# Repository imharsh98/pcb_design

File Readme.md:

# PCB Design Internship

## Overview

This repository contains the complete PCB schematics and layouts for digital circuits (555 flasher, arduino microcontroller, decade counter, voltage regulator), ensuring correct pin-mapping and power integrity. This work was undertaken during an internship which the author attended for his BTech requirements. The internship was done at the company named Core Future.

## Repository Structure

```

├── designs/
│   ├── 555flasher/
    │   ├── 555flasher.brd                          # Board file for the 555flasher project
    │   ├── 555flasher.sch                          # Schematic file for the 555flasher project
    |
    ├── arduino/
    │   ├── arduino.brd    
    │   ├── arduino.sch
    |
    ├── decade_counter/
    │   ├── d_counter.brd   
    │   ├── d_counter.sch
    |   ├── d_counter_brd.png                       # PNG file of the decade counter schematic
    | 
    ├── voltage_regulator/
    │   ├── v_regulator.brd
        ├── v_regulator.sch                
│
├── pcb designs/
│   └── contains library files
|
├── practice-designs/
│   └── contains some unorganized practice designs and can be ignored
│
├── README.md                                       # This file (main guide)
```

## Project 1: 555 Timer LED Flasher (`555flasher.brd`)

*   **Description:** An astable multivibrator circuit using the LM555 timer.
*   **Highlights:** Ground plane implementation and power trace width management.

## Project 2: Arduino Compatible Board (`arduino.brd`)

*   **Description:** A custom microcontroller board layout based on the Arduino architecture.
*   **Highlights:**
    *   **Clock Stability:** Optimized placement of the Crystal Oscillator near the MCU.
    *   **Power Integrity:** Strategic placement of decoupling capacitors.

## Project 3: Digital Counter (`d_counter.brd`)

*   **Description:** A digital logic circuit for counting applications.
*   **Highlights:**
    *   **Signal Routing:** Managed routing for multiple logic gates and clock lines.

## Project 4: Voltage Regulator (`v_regulator.brd`)

*   **Description:** A power supply circuit designed to provide a stable DC output from a varying input voltage.
*   **Highlights:**
    *   **Thermal Management:** Copper polygon pours utilized for heat dissipation.
    *   **Power Routing:** Wide traces designed for high-current paths to minimize voltage drop.

---
### General Technical Details
*   **Tool Used:** Eagle CAD for layout and PnR (Placement and Routing); Proteus for circuit schematic creation.
*   **Steps for Replication:** Run the .sch file in Proteus and the .brd file in Eagle CAD. 
*   **Board Specs:** 2-Layer PCBs (Top/Bottom Copper)
*   **DFM:** Designed with through-hole components for ease of prototyping.

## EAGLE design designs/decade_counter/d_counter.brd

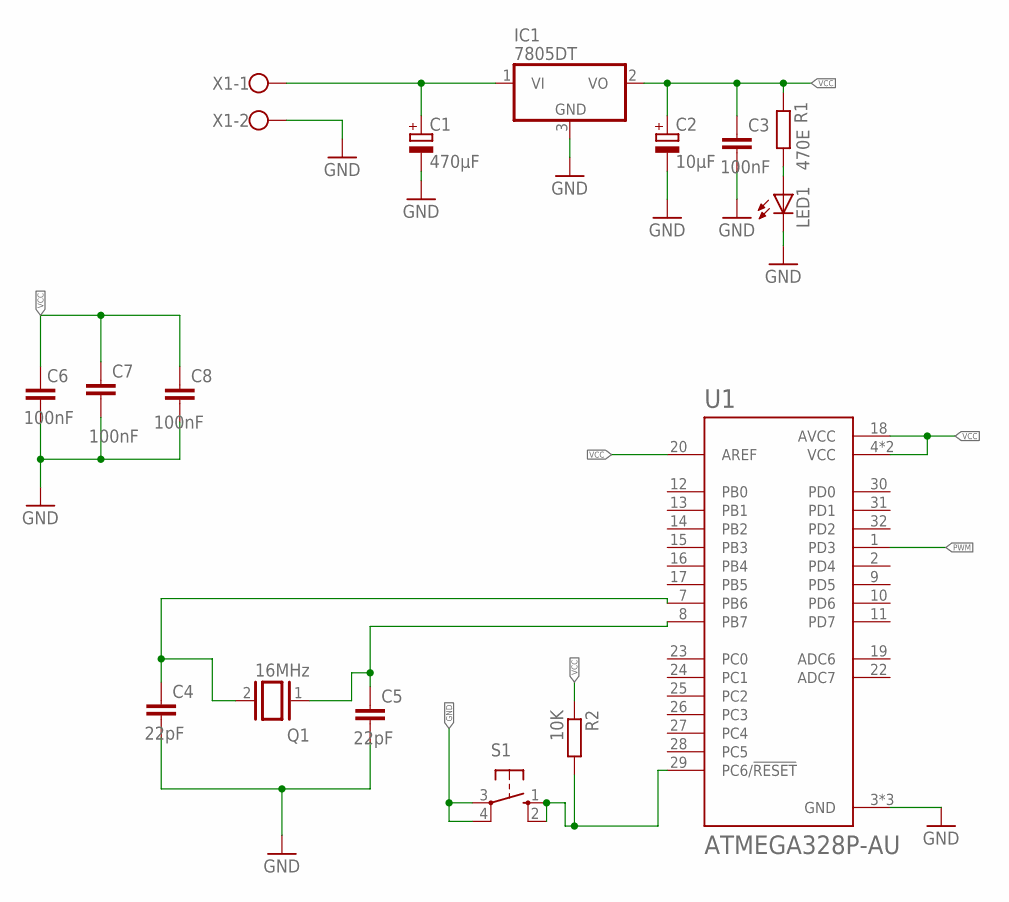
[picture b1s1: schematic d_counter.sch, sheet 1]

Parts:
C1: 470µF; 150CLZ-1010
C2: 10µF; 150CLZ-1010
C3, C6, C7, C8: 100nF; C1206
C4, C5: 22pF; C1206
IC1: 7805DT; TO252
LED1: LEDSMT1206; 1206
Q1: 16MHz; QS
R1: 470E; M1206
R2: 10K; R1206
S1: 10-XX; B3F-10XX
U1: ATMEGA328P-AU; QFP80P900X900X120-32N
X1: W237-102

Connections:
GND: C1.-, C2.-, C3.2, C4.2, C5.2, C6.2, C7.2, C8.2, IC1.3 (GND), LED1.C, S1.3, S1.4 (P1), U1.3 (GND), U1.5 (GND), U1.21 (GND), X1.2; also elsewhere on the board
unnamed: C1.+, IC1.1 (VI), X1.1
unnamed: LED1.A, R1.2
unnamed: C4.1, Q1.2, U1.7 (PB6)
unnamed: C5.1, Q1.1, U1.8 (PB7)
unnamed: R2.2, S1.1 (S), S1.2 (S1), U1.29 (PC6/!RESET)
PWM: U1.1 (PD3); also elsewhere on the board
VCC: C2.+, C3.1, C6.1, C7.1, C8.1, IC1.2 (VO), R1.1, R2.1, U1.4 (VCC), U1.6 (VCC), U1.18 (AVCC), U1.20 (AREF); also elsewhere on the board

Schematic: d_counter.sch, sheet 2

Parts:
IC2: 74AC08D; SO14
IC3, IC4, IC5, IC6: 4017D; SO16
LED2, LED3, LED4, LED5, LED6, LED7, LED8, LED9, LED10, LED11, LED12, LED13, LED14, LED15, LED16, LED17, LED18, LED19, LED20, LED21, LED22, LED23, LED24, LED25, LED26, LED27, LED28, LED29, LED30, LED31, LED32, LED33: LEDSML1206; SML1206
R3: 330E; R1206

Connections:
1: IC3.15 (RES), IC6.11 (Q9)
2: IC2.3 (O), IC4.14 (CLK)
3: IC3.3 (Q0), IC4.15 (RES)
4: IC2.6 (O), IC5.14 (CLK)
5: IC4.3 (Q0), IC5.15 (RES)
6: IC2.8 (O), IC6.14 (CLK)
7: IC5.3 (Q0), IC6.15 (RES)
8: IC3.2 (Q1), LED2.A
9: IC3.4 (Q2), LED3.A
10: IC3.7 (Q3), LED4.A
11: IC3.10 (Q4), LED5.A
12: IC3.1 (Q5), LED6.A
13: IC3.5 (Q6), LED7.A
14: IC3.6 (Q7), LED8.A
15: IC3.9 (Q8), LED9.A
16: IC4.2 (Q1), LED10.A
17: IC4.4 (Q2), LED11.A
18: IC4.7 (Q3), LED12.A
19: IC4.10 (Q4), LED13.A
20: IC4.1 (Q5), LED14.A
21: IC4.5 (Q6), LED15.A
22: IC4.6 (Q7), LED16.A
23: IC4.9 (Q8), LED17.A
24: IC5.2 (Q1), LED18.A
25: IC5.4 (Q2), LED19.A
26: IC5.7 (Q3), LED20.A
27: IC5.10 (Q4), LED21.A
28: IC5.1 (Q5), LED22.A
29: IC5.5 (Q6), LED23.A
30: IC5.6 (Q7), LED24.A
31: IC5.9 (Q8), LED25.A
32: IC6.2 (Q1), LED26.A
33: IC6.4 (Q2), LED27.A
34: IC6.7 (Q3), LED28.A
35: IC6.10 (Q4), LED29.A
36: IC6.1 (Q5), LED30.A
37: IC6.5 (Q6), LED31.A
38: IC6.6 (Q7), LED32.A
39: IC6.9 (Q8), LED33.A
GND: IC2.7 (GND), IC3.8 (VSS), IC4.8 (VSS), IC5.8 (VSS), IC6.8 (VSS), IC6.13 (ENA), R3.1; also elsewhere on the board
unnamed: IC2.1 (I0), IC3.11 (Q9), IC3.13 (ENA)
unnamed: IC2.4 (I0), IC4.11 (Q9), IC4.13 (ENA)
unnamed: IC2.9 (I0), IC5.11 (Q9), IC5.13 (ENA)
unnamed: LED2.C, LED3.C, LED4.C, LED5.C, LED6.C, LED7.C, LED8.C, LED9.C, LED10.C, LED11.C, LED12.C, LED13.C, LED14.C, LED15.C, LED16.C, LED17.C, LED18.C, LED19.C, LED20.C, LED21.C, LED22.C, LED23.C, LED24.C, LED25.C, LED26.C, LED27.C, LED28.C, LED29.C, LED30.C, LED31.C, LED32.C, LED33.C, R3.2
PWM: IC2.2 (I1), IC2.5 (I1), IC2.10 (I1), IC3.14 (CLK); also elsewhere on the board
VCC: IC2.14 (VCC), IC3.16 (VDD), IC4.16 (VDD), IC5.16 (VDD), IC6.16 (VDD); also elsewhere on the board

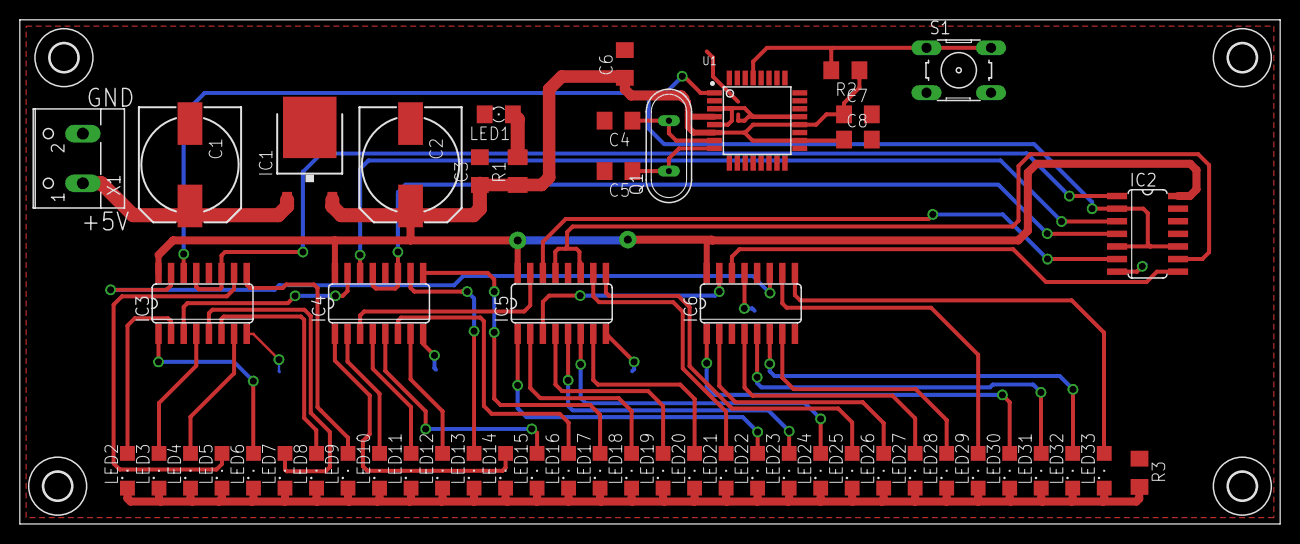
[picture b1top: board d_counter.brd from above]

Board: 2 copper layers, 127.0 x 50.8 mm, 58 parts (0 on the bottom side), 51 nets.

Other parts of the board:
U$1, U$2, U$3, U$5: 2,8

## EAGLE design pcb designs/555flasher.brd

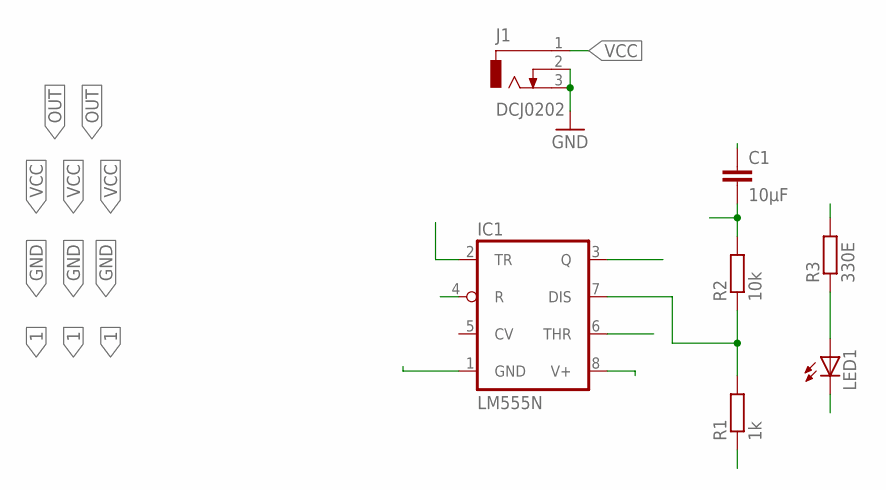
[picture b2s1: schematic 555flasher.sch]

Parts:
C1: 10µF; C025-025X050
IC1: LM555N; DIL08
J1: DCJ0202
LED1: LED5MM
R1: 1k; 0207/10
R2: 10k; 0207/10
R3: 330E; 0207/10

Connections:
1: C1.2, IC1.2 (TR), IC1.6 (THR), R2.2
GND: C1.1, IC1.1 (GND), J1.2, J1.3, LED1.K (C)
unnamed: IC1.7 (DIS), R1.2, R2.1
unnamed: LED1.A, R3.1
OUT: IC1.3 (Q), R3.2
VCC: IC1.4 (R), IC1.8 (V+), J1.1, R1.1

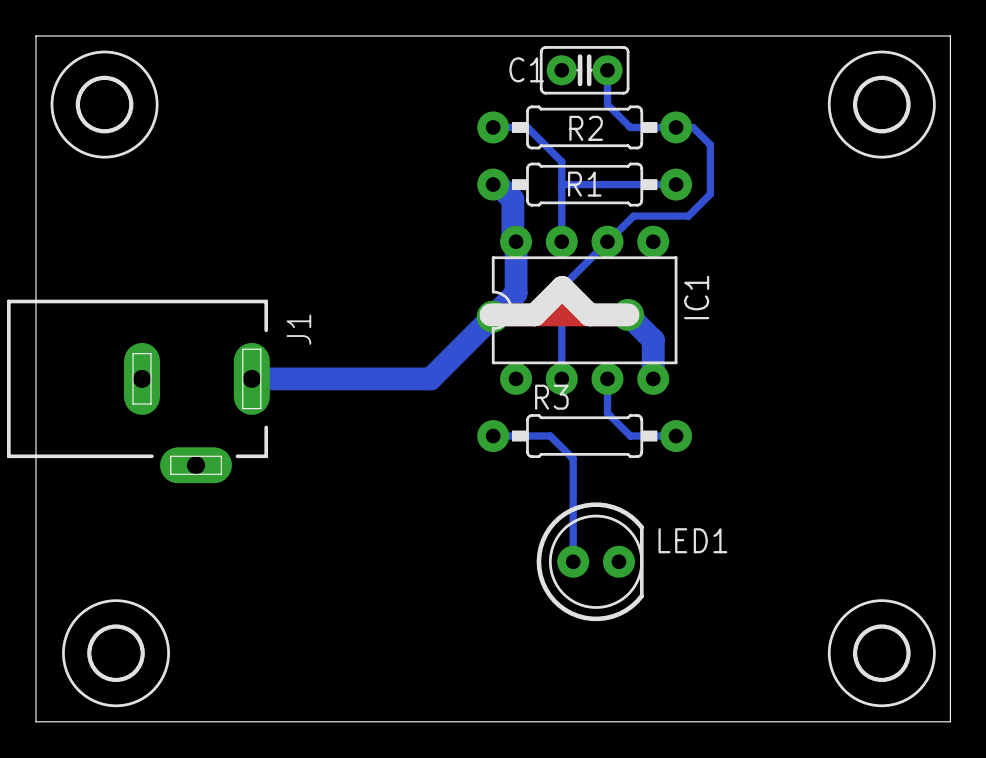
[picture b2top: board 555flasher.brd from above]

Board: 2 copper layers, 50.8 x 38.1 mm, 11 parts (0 on the bottom side), 6 nets.

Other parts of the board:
U$1, U$2, U$3, U$4: 2,8

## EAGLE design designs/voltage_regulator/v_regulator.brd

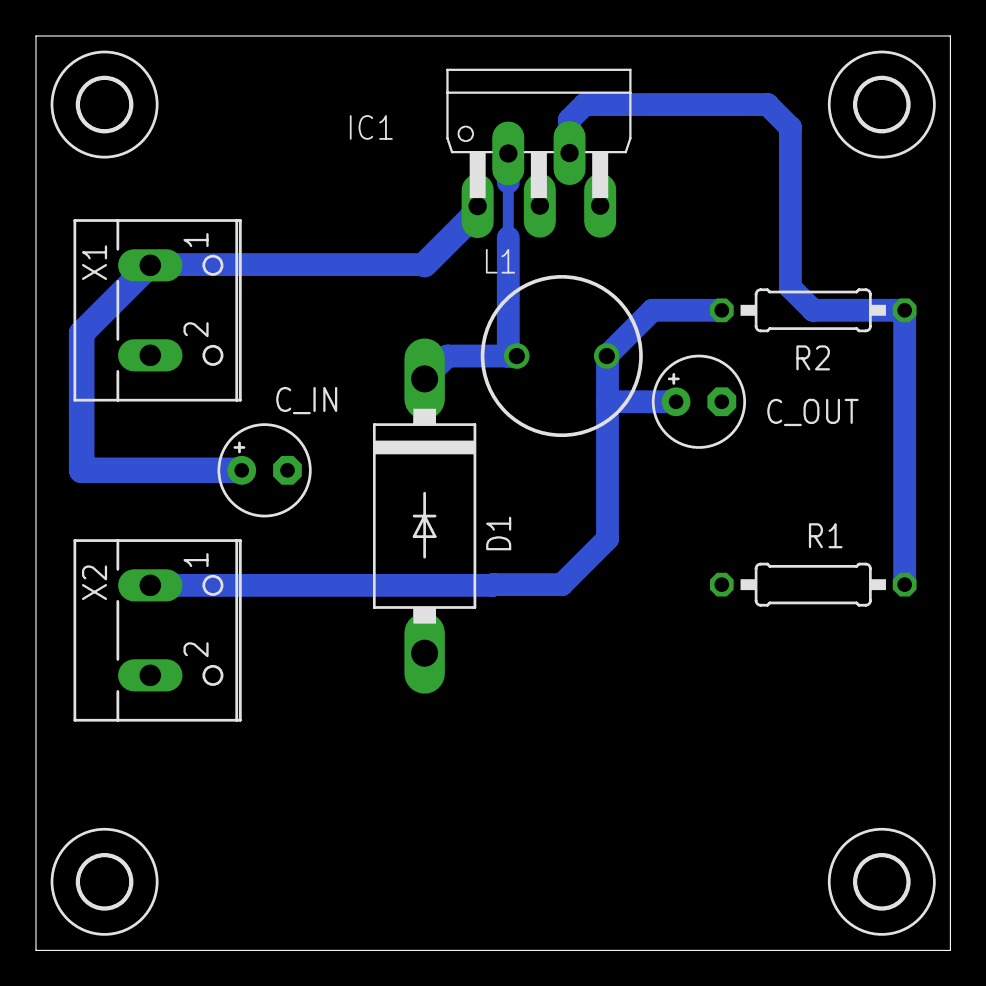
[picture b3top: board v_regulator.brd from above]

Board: 2 copper layers, 50.8 x 50.8 mm, 13 parts (0 on the bottom side), 5 nets.

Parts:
C_IN: 100µF; E2,5-5
C_OUT: 469µF; E2,5-5
D1: 1N5624; DO201-15
IC1: TO220-5_STAGGERED
L1: 68µH; 6000-XXXX-RC
R1: 3.6k; 0207/10
R2: 11k; 0207/10
U$1, U$2, U$3, U$4: 2,8
X1: 12V; W237-102
X2: W237-102

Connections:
GND: C_IN.-, C_OUT.-, D1.A, IC1.P$3, IC1.P$5, R1.1, X1.2, X2.2
unnamed: D1.C, IC1.P$2, L1.1
unnamed: IC1.P$4, R1.2, R2.1
V_IN: C_IN.+, IC1.P$1, X1.1
V_OUT: C_OUT.+, L1.2, R2.2, X2.1

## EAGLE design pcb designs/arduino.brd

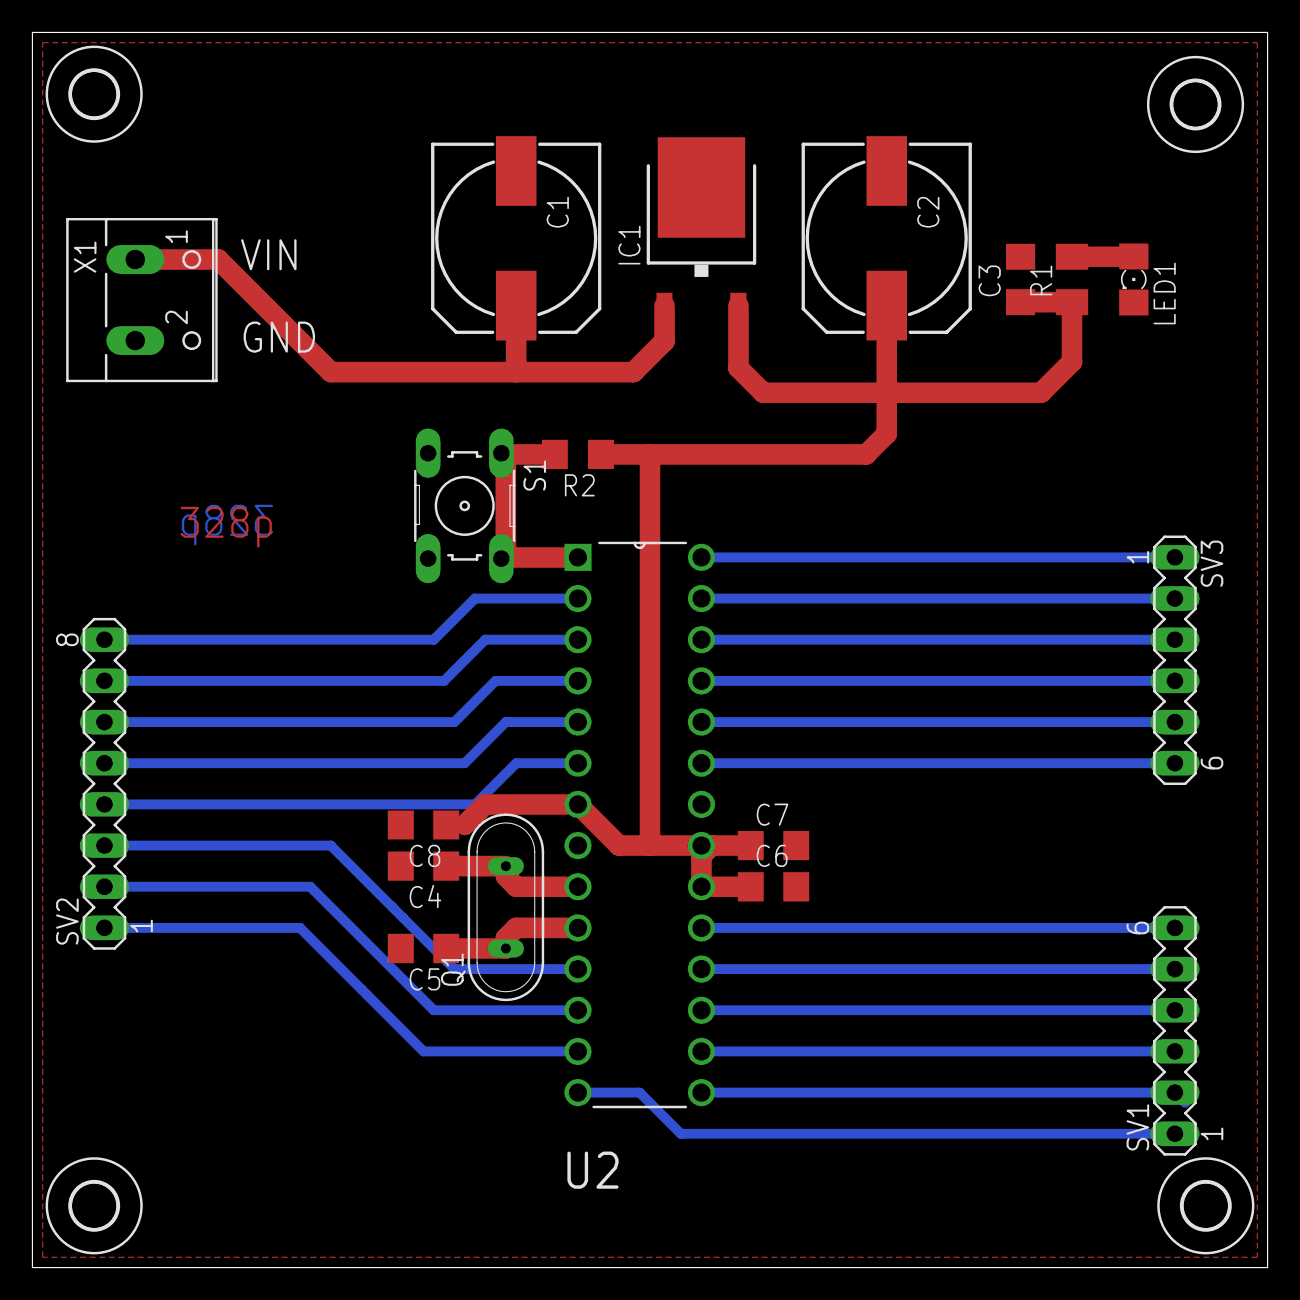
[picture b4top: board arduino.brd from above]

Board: 2 copper layers, 76.2 x 76.2 mm, 23 parts (0 on the bottom side), 27 nets.

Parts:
C1: 470µF; 150CLZ-1010
C2: 10µF; 150CLZ-1010
C3, C6, C7, C8: 100nF; C1206
C4, C5: 22pF; C1206
IC1: 7805DT; TO252
LED1: 1206
Q1: 16MHz; QS
R1: 470E; M1206
R2: 10K; R1206
S1: B3F-10XX
SV1, SV3: MA06-1
SV2: MA08-1
U2: ATMEGA328P-PU; DIP254P762X457-28
U$1, U$2, U$3, U$4: 2,8
X1: W237-102

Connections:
A0: SV3.6, U2.23
A1: SV3.5, U2.24
A2: SV3.4, U2.25
A3: SV3.3, U2.26
A4: SV3.2, U2.27
A5: SV3.1, U2.28
D0: SV2.8, U2.2
D1: SV2.7, U2.3
D2: SV2.6, U2.4
D3: SV2.5, U2.5
D4: SV2.4, U2.6
D5: SV2.3, U2.11
D6: SV2.2, U2.12
D7: SV2.1, U2.13
D8: SV1.1, U2.14
D9: SV1.2, U2.15
D10: SV1.3, U2.16
D11: SV1.4, U2.17
D12: SV1.5, U2.18
D13: SV1.6, U2.19
GND: C1.-, C2.-, C3.2, C4.2, C5.2, C6.2, C7.2, C8.2, IC1.3, LED1.C, S1.3, S1.4, U2.8, U2.22, X1.2
unnamed: C1.+, IC1.1, X1.1
unnamed: LED1.A, R1.2
unnamed: C4.1, Q1.2, U2.9
unnamed: C5.1, Q1.1, U2.10
unnamed: R2.2, S1.1, S1.2, U2.1
VCC: C2.+, C3.1, C6.1, C7.1, C8.1, IC1.2, R1.1, R2.1, U2.7, U2.20, U2.21

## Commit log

2025-03-20 [Commit-1] All available code
2025-07-26 [Commit 2] Add Readme and board view for decade counter
2026-01-18 [Commit 3] Update README with project details and specs
    Added project descriptions and general technical details to the README.
2026-03-25 [Commit 3] Modify the Readme file
2026-03-25 [Commit 4] Rectify the Readme file
